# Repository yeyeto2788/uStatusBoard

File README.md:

# uStatusBoard
The uStatusBoard is a board designed to be used as simple notifier with 4 leds WS2812B (aka NeoPixels) to show the status
by changing the color of the led on the board.

You can use a marker to write down the condition/status of anything you're monitoring.

**Top view of the board (latest version)**

**Bottom view of the board (latest version)**

In order to use the board we will need a Wemos D1 mini (image below) which the board is soldered onto it.

**Wemos D1 mini board**

**Note:** There is no need to use specifically the Wemos D1 mini board, another board can used with this uStatusBoard.

## Structure for the Repository

```
Main Repository Folder(uStatusBoard)
        └── docs Folders
        |        |
        |        └── images folder
        └── examples Folder
        |   |
        |   └── example scripts
        |     
        ├── hardware Folder
        |     |
        |     └── version folders (Schematics and board design)
        |
        └── status_board.py (module)
        |
        └── README (This document.)
```

## Usage examples
To use the code (written in [MicroPython](https://micropython.org/)) we will just upload the module `status_board.py` and in the REPL we can start playing with it.

```console
>>> from status_board import StatusBoard
>>> board = StatusBoard()
>>> board.pin
Pin(15)
>>> board.brightness
255
```

Take into account that we are instantiated the object with the default attributes as seen in the REPL output above.

So now let's play a bit with it.

```console
>>> board.color_all('blue')
>>> board.color_all('red')
>>> board.color_all('green')
>>> board.color_all('white')
>>> board.color_all('nocolor')
```

This colors are defined on the `StatusBoard.colors` attribute which can be accessed any time

```console
>>> board.colors
{'cyan': [0, 1, 1], 'nocolor': [0, 0, 0], 'magenta': [1, 0, 1], 'blue': [0, 0, 1], 'yellow': [1, 1, 0], 'white': [1, 1, 1], 'green': [0, 1, 0], 'red': [1, 0, 0]}
```

Now let's turn off all the leds

```console
>>> board.clear_all()
```

If you want to know more about what methods the `StatusBoard` has head over to the [status_board.py](./status_board.py) script.

#### If you want **more examples** head over the [examples folder](./examples/).

___
## Any feedback is highly appreciated! 

Please, if you see any error open an issue on this repo.

___
## Useful links:

[MicroPython](https://micropython.org/)

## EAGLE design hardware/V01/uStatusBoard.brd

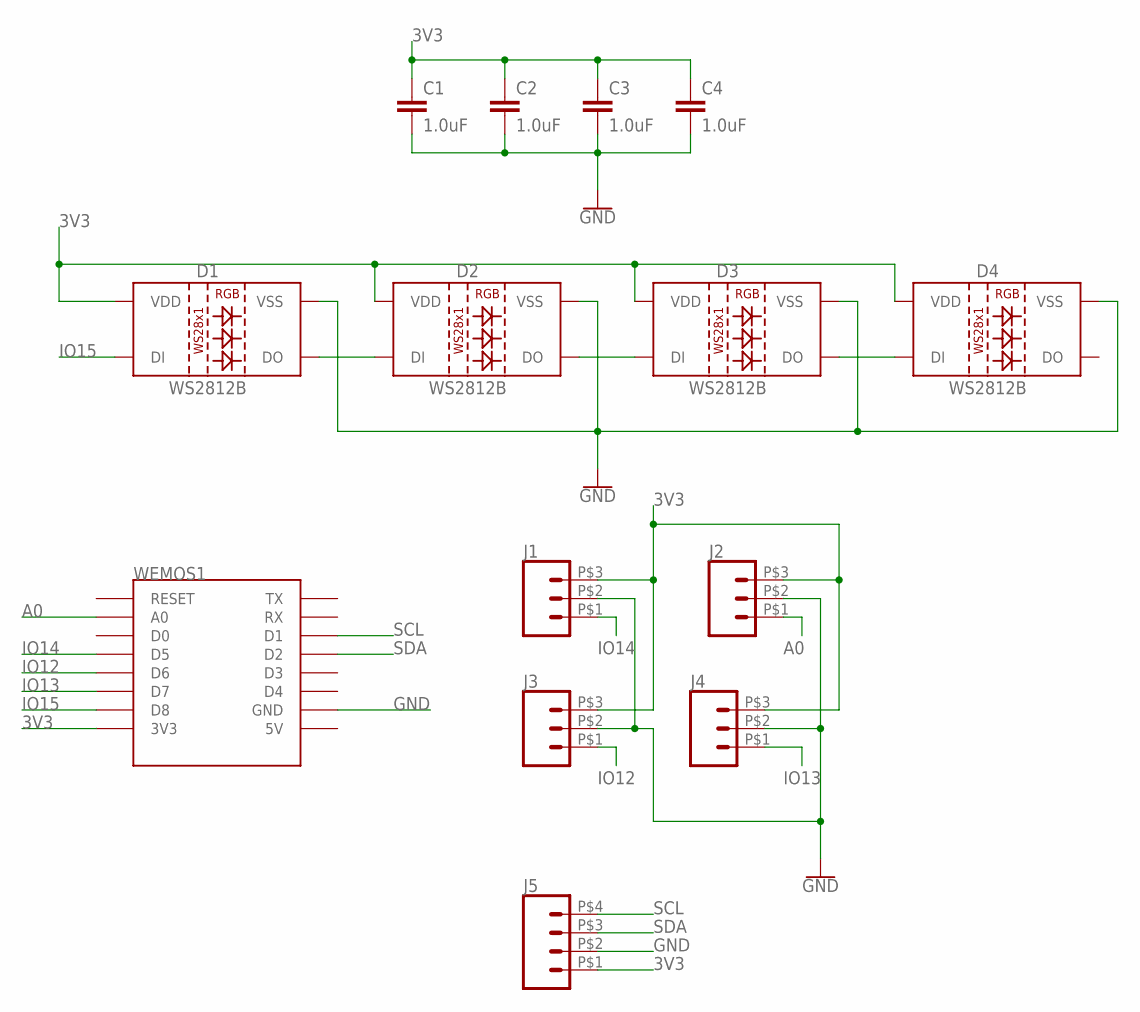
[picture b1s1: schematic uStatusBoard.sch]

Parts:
C1, C2, C3, C4: 1.0uF; 0805
D1, D2, D3, D4: WS2812B
J1, J2, J3, J4: CONN_031X03_SMD; 1X03_SMD
J5: CONN_041X04_SMD; 1X04_SMD
WEMOS1: WEMOS-D1-MINIWEMOS_SMD; WEMOS-SMD

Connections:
3V3: C1.1, C2.1, C3.1, C4.1, D1.1 (VDD), D2.1 (VDD), D3.1 (VDD), D4.1 (VDD), J1.P$3 (3), J2.P$3 (3), J3.P$3 (3), J4.P$3 (3), J5.P$1 (1), WEMOS1.3V3
A0: J2.P$1 (1), WEMOS1.A0
GND: C1.2, C2.2, C3.2, C4.2, D1.3 (VSS), D2.3 (VSS), D3.3 (VSS), D4.3 (VSS), J1.P$2 (2), J2.P$2 (2), J3.P$2 (2), J4.P$2 (2), J5.P$2 (2), WEMOS1.GND
IO12: J3.P$1 (1), WEMOS1.D6
IO13: J4.P$1 (1), WEMOS1.D7
IO14: J1.P$1 (1), WEMOS1.D5
IO15: D1.4 (DI), WEMOS1.D8
unnamed: D1.2 (DO), D2.4 (DI)
unnamed: D2.2 (DO), D3.4 (DI)
unnamed: D3.2 (DO), D4.4 (DI)
SCL: J5.P$4 (4), WEMOS1.D1
SDA: J5.P$3 (3), WEMOS1.D2

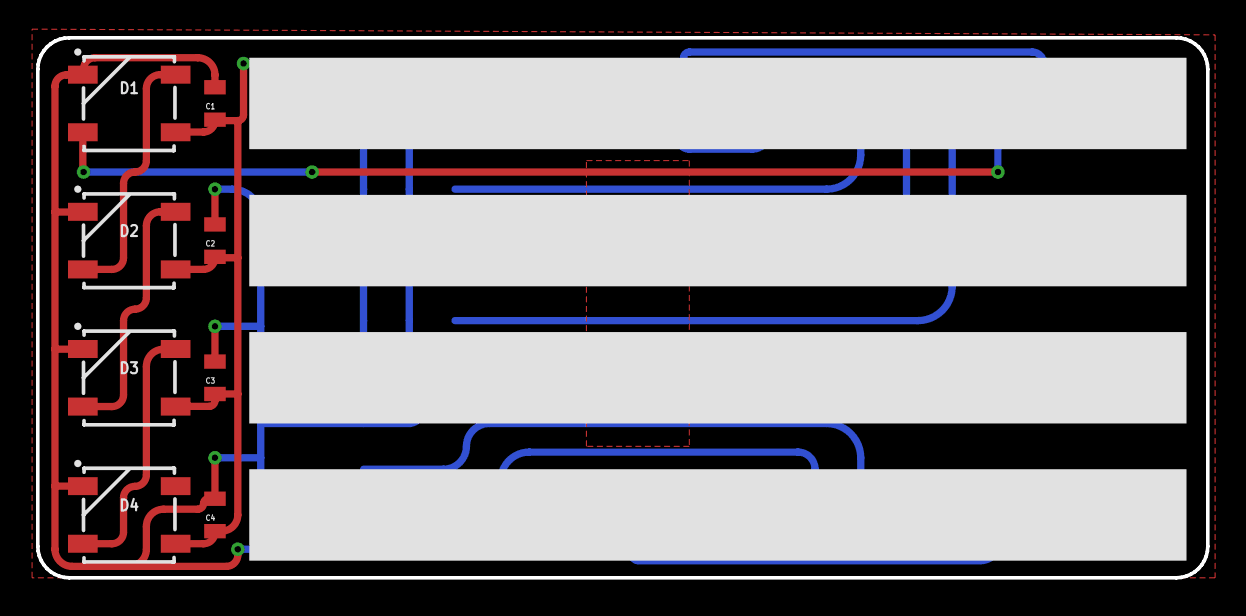
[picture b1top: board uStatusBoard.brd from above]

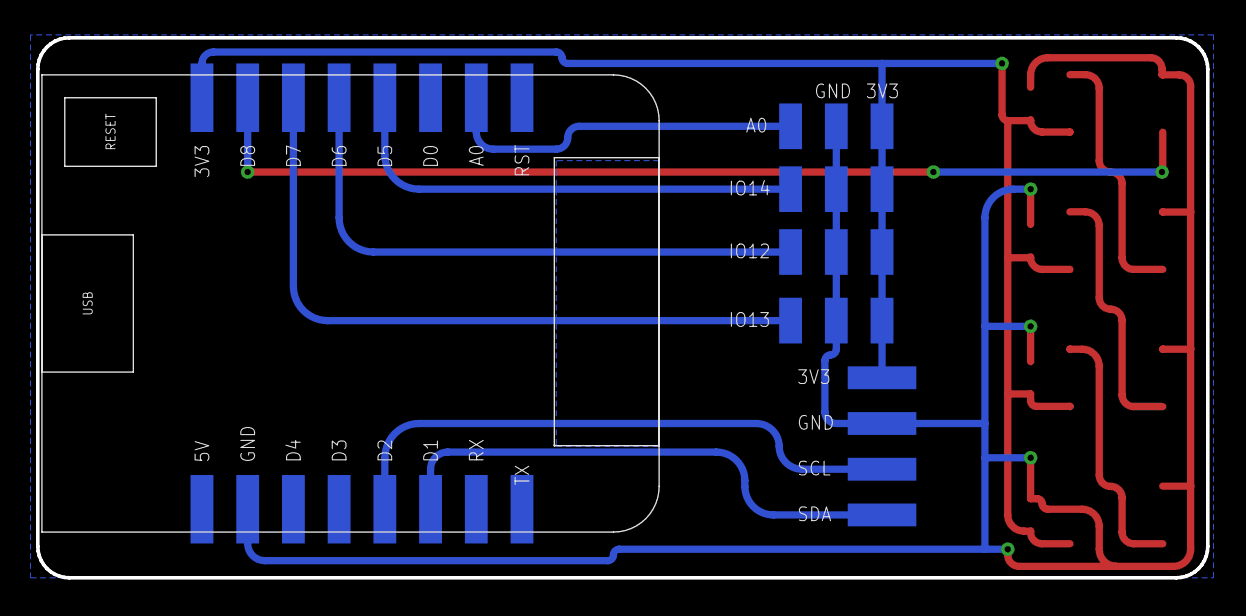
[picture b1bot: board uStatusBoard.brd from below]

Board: 2 copper layers, 65.0 x 30.0 mm, 14 parts (6 on the bottom side), 12 nets.

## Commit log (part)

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2019-05-28 First commit to repo with basic module and basic usage of it.
2019-05-28 Fix typos on module and add new function
2019-05-28 Add functions and new methods usage of the module
2019-05-28 Add images to repo and README and some info on the file.
2019-05-28 Add hardware v2 files and reflect changes on the README.
2019-05-28 Add some class documentation.
2019-05-29 Add another usage example of the board and fix typo on image naming.
2019-05-30 Fix some lint issues
2019-05-30 Add other methods to module, documents examples and add new example
2019-05-31 Add basic NOT_TESTED jenkins demo
2019-06-03 Add documentation to the methods and so on.
2021-08-24 Lint and format files
2021-08-24 Generate release file.
2021-08-24 Add example with server
2022-02-18 Add poetry as development tool and pre-commit hooks
2024-03-20 Bump black from 22.1.0 to 24.3.0
    Bumps [black](https://github.com/psf/black) from 22.1.0 to 24.3.0.
    - [Release notes](https://github.com/psf/black/releases)
    - [Changelog](https://github.com/psf/black/blob/main/CHANGES.md)
    - [Commits](https://github.com/psf/black/compare/22.1.0...24.3.0)
    ---
    updated-dependencies:
2025-01-13 Bump virtualenv from 20.13.1 to 20.26.6
    Bumps [virtualenv](https://github.com/pypa/virtualenv) from 20.13.1 to 20.26.6.
    - [Release notes](https://github.com/pypa/virtualenv/releases)
    - [Changelog](https://github.com/pypa/virtualenv/blob/main/docs/changelog.rst)
    - [Commits](https://github.com/pypa/virtualenv/compare/20.13.1...20.26.6)
    ---
    updated-dependencies:
2026-01-13 Bump virtualenv from 20.26.6 to 20.36.1
    Bumps [virtualenv](https://github.com/pypa/virtualenv) from 20.26.6 to 20.36.1.
    - [Release notes](https://github.com/pypa/virtualenv/releases)
    - [Changelog](https://github.com/pypa/virtualenv/blob/main/docs/changelog.rst)
    - [Commits](https://github.com/pypa/virtualenv/compare/20.26.6...20.36.1)
    ---
    updated-dependencies:

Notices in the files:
parts and their libraries:
SparkFun-LED: Licensing: Creative Commons ShareAlike 4.0 International - https://creativecommons.org/licenses/by-sa/4.0
